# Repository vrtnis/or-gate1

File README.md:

# or-gate1

A simple OR gate built using atopile. Read more at https://atopile.io/first_project/

Watch the related video at [YouTube](https://www.youtube.com/watch?v=q-ztnUD7CZo)

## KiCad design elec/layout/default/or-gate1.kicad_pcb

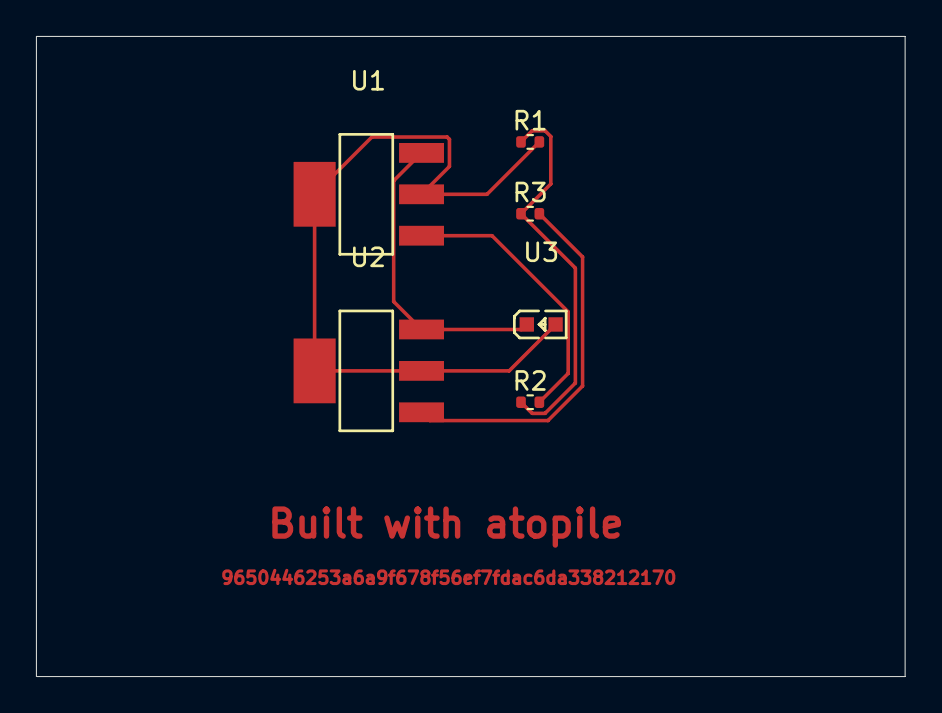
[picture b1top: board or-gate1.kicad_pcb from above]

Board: 2 copper layers, 48.3 x 35.6 mm, 6 parts (0 on the bottom side), 5 nets.

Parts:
R1: 10.0 +/- 1.0 kiloohm; R0402
R2, R3: 1.0 +/- 0.10000000000000003 kiloohm; R0402
U1, U2: SOT-223-3_L6.5-W3.4-P2.30-LS7.0-BR
U3: LED0603-RD

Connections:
b: R2.2, U1.1
b-1: R3.2, U2.1
c: R1.2, U1.2, U1.4, U2.2, U2.4, U3.2
e: U1.3, U2.3, U3.1
vcc: R1.1, R2.1, R3.1

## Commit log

2024-02-08 Configure project
2024-02-08 Initial commit with OR gate
2024-02-08 Remove .github/workflows directory
2024-02-12 fix dependencies
2024-02-12 add CI
2024-02-14 Updated build folder
2024-02-14 Update layout
2024-02-15 Do layout
2024-02-15 Update PCB with git hash and logo
2024-02-15 add routes
